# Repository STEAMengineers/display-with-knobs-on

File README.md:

# display-with-knobs-on

Think [cheap yellow display](https://github.com/witnessmenow/ESP32-Cheap-Yellow-Display) but not necessarily yellow and with two joystick inputs and four channels of brushed motor output. Originally designed to control [The open source underwater vehicle](https://github.com/concretedog/Tiny-Opensource-Underwater-Vehicle-TOUV-) project. 

## Features

* [RP2350b](https://datasheets.raspberrypi.com/rp2350/rp2350-product-brief.pdf) - Dual Arm Cortex-M33 or dual Hazard3 RISC-V processors
@ 150MHz
* [W25Q128JV-DTR](https://www.winbond.com/resource-files/w25q128jv_dtr%20revc%2003272018%20plus.pdf) - 16Mb primary flash 
* [MSP3520 screen](https://www.lcdwiki.com/3.5inch_SPI_Module_ILI9488_SKU%3AMSP3520) - ILI9488 powered 320x480 LCD screen with resistive touch and SD card slot (Headers)
* 2 x [TB6612FNG](https://toshiba.semicon-storage.com/us/product/linear/motordriver/detail.TB6612FNG.html) - Four channels of brushed motor outputs
* [IP5310](https://www.injoinic.com/api//static/uploads/20250528/20250528180445_6836dfbd54166.pdf) - Battery charger management with 3A boost output @ 5V for motors
* 2 x Joystick - Two axis analoge joysticks with push button inputs

  ## GPIO

  ### Motors

  A
  * IN1 - GPIO29
  * IN2 - GPIO28
  * PWM - GPIO24

  B
  * IN1 - GPIO31
  * IN2 - GPIO32
  * PWM - GPIO25

  STANDBY - GPIO30

  C
  * IN1 - GPIO34
  * IN2 - GPIO33
  * PWM - GPIO26

  D
  * IN1 - GPIO36
  * IN2 - GPIO37
  * PWM - GPIO27

  STANDBY - GPIO35

  ### Joysticks
  A
  * X - GPIO43
  * Y - GPIO44
  * Button - GPIO39
 
  B
  * X - GPIO41
  * Y - GPIO42
  * Button - GPIO38
 
  ### Screen

  Display
  * CS - GPIO13
  * RESET - GPIO18
  * DC/RS - GPIO17
  * MOSI - GPIO11
  * MISO - GPIO12
  * SCK - GPIO14
  * LED - GPIO16
 
  Touch
  * CS - GPIO10
  * IRQ - GPIO15
  * MOSI - GPIO11
  * MISO - GPIO12
  * SCK - GPIO14
 
  SD card
  * CS - GPIO21
  * SCK - GPIO22
  * MOSI - GPIO19
  * MISO - GPIO20

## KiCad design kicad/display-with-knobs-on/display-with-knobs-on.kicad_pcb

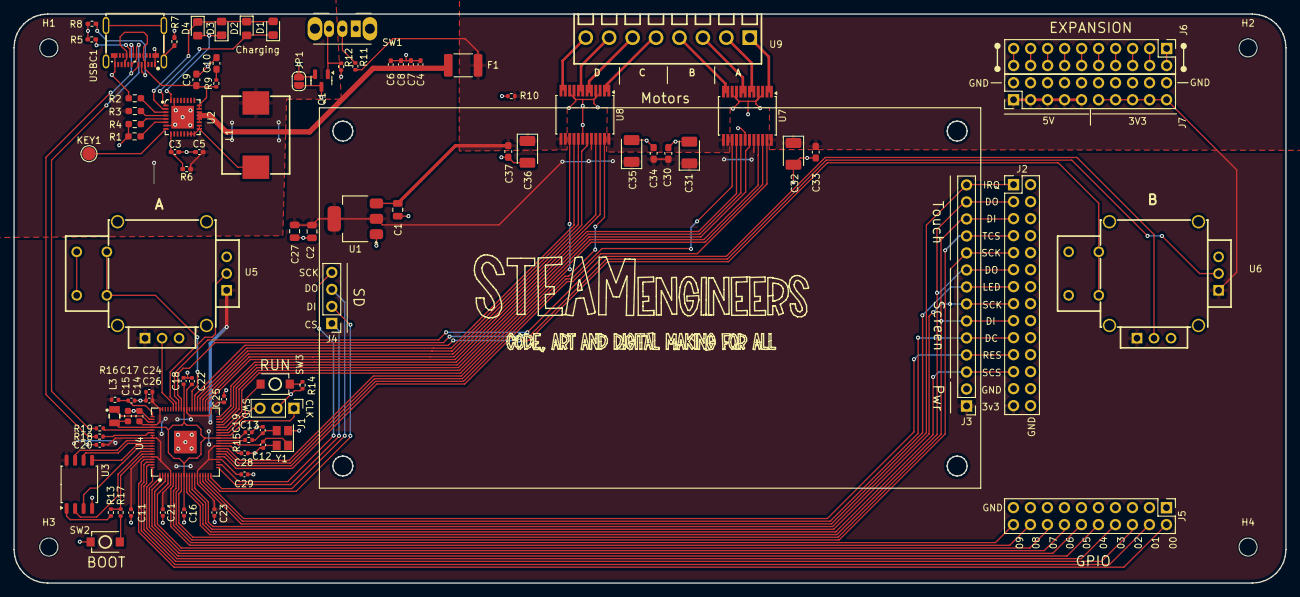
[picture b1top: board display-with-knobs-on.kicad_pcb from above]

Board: 2 copper layers, 190.0 x 85.0 mm, 92 parts (1 on the bottom side), 106 nets.

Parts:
C1, C2, C27: 10u; C_0805_2012Metric
C3, C4, C5, C6, C7, C8: 22uF; C_0402_1005Metric_Pad0.74x0.62mm_HandSolder
C9, C10: 10uF; C_0603_1608Metric_Pad1.08x0.95mm_HandSolder
C11, C16, C19, C20, C21, C22, C23, C24, C25, C26, C28, C29: 100n; C_0402_1005Metric
C12, C13: 15p; C_0402_1005Metric
C14, C15: 4.7u; C_0603_1608Metric
C17, C18: 4.7u; C_0402_1005Metric
C30, C33, C34, C37: 0.1uF; C_0603_1608Metric_Pad1.08x0.95mm_HandSolder
C31, C32, C35, C36: 10uF; CP_EIA-3528-21_Kemet-B_Pad1.50x2.35mm_HandSolder
CN1: S2B-PH-SM4-TB(LF)(SN); CONN-SMD_P2.00_S2B-PH-SM4-TB-LF-SN
D1, D2, D3, D4: LED; LED_0805_2012Metric_Pad1.15x1.40mm_HandSolder
F1: Polyfuse; Fuse_1812_4532Metric_Pad1.30x3.40mm_HandSolder
H1, H2, H3, H4: MountingHole; MountingHole_2.7mm_M2.5
J1: Conn_01x03_Pin; PinHeader_1x03_P2.54mm_Vertical
J2: Conn_02x14_Odd_Even; PinHeader_2x14_P2.54mm_Vertical
J3: Conn_01x14_Socket; PinHeader_1x14_P2.54mm_Vertical
J4: Conn_01x04_Socket; PinHeader_1x04_P2.54mm_Vertical
J5, J6, J7: Conn_02x10_Odd_Even; PinHeader_2x10_P2.54mm_Vertical
JP1: Jumper_on; SolderJumper-2_P1.3mm_Open_RoundedPad1.0x1.5mm
KEY1: TestPoint; TestPoint_Pad_D2.0mm
L1: MHCC10040-1R0M-R7; IND-SMD_L11.6-W10.1
L3: 3.3u; IND-SMD_L2.0-W1.6_AOTA-B201610S3R3-101-T
Q1: JSM2302; SOT-23
R1: 51K; R_0603_1608Metric_Pad0.98x0.95mm_HandSolder
R2, R3, R4: 0; R_0603_1608Metric_Pad0.98x0.95mm_HandSolder
R5, R8: 5.1K; R_0402_1005Metric_Pad0.72x0.64mm_HandSolder
R6: 0; R_0402_1005Metric_Pad0.72x0.64mm_HandSolder
R7: 1M; R_0402_1005Metric_Pad0.72x0.64mm_HandSolder
R9: 2R; R_0402_1005Metric
R10: R120; R_0402_1005Metric
R11: 10K; R_0402_1005Metric
R12: 100K; R_0402_1005Metric
R13: 0; R_0402_1005Metric
R14, R15, R17: 1k; R_0402_1005Metric
R16: 33; R_0402_1005Metric
R18, R19: 27; R_0402_1005Metric
SW1: ON/OFF; SW_Slide_SPDT_Angled_CK_OS102011MA1Q
SW2, SW3: SW_Push; SW-SMD_L3.9-W3.0-P4.45
U1: NCP1117-3.3_SOT223; SOT-223-3_TabPin2
U2: IP5310; QFN-32_L5.0-W5.0-P0.50-BL-EP3.4
U3: W25Q128JVS; SOIC-8_5.23x5.23mm_P1.27mm
U4: RP2350_80QFN; QFN-80_L10.0-W10.0-P0.40-TL-EP3.4
U5, U6: YF16S-FL7.2-B5KB(45-10)-Y; JOYTICK-TH_YF16S-FL7.2-B5KB-45-10-Y_1
U7, U8: TB6612FNG; SSOP-24_5.3x8.2mm_P0.65mm
U9: DB125-3.5-8P-GN-S; CONN-TH_8P-P3.50_DORABO_DB125-3.5-8P-GN-S
USBC1: 105450-0101; USB-C-SMD_TYPE-C-USB-18
Y1: ABM8-272-T3; Crystal_SMD_3225-4Pin_3.2x2.5mm

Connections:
+1V1: C15.1, C16.1, C18.1, C19.1, L3.1, U4.10 (DVDD), U4.32 (DVDD), U4.51 (DVDD), U4.65 (VREG_FB)
+3V3: C2.1, C11.1, C14.1, C20.1, C21.1, C22.1, C23.1, C24.1, C25.1, C26.1, C27.1, C28.1, C29.1, C30.1, C31.1, C34.1, C35.1, J2.27, J3.1, J7.11, J7.13, J7.15, J7.17, J7.19, R16.1, U1.2 (VO), U3.8 (VCC), U4.5 (IOVDD), U4.15 (IOVDD), U4.24 (IOVDD), U4.29 (IOVDD), U4.41 (IOVDD), U4.50 (IOVDD), U4.59 (ADC_AVDD), U4.60 (IOVDD), U4.64 (VREG_VIN), U4.68 (USB_OTP_VDD), U4.69 (QSPI_IOVDD), U4.76 (IOVDD), U5.1, U5.4, U6.1, U6.4, U7.20 (VCC), U8.20 (VCC)
+5V: C1.1, C32.1, C33.1, C36.1, C37.1, F1.1, J7.1, J7.3, J7.5, J7.7, J7.9, R10.2, R11.1, U1.3 (VI), U7.13 (VM2), U7.14 (VM3), U7.24 (VM1), U8.13 (VM2), U8.14 (VM3), U8.24 (VM1)
+BATT: C5.1, CN1.2, L1.2, R3.1, R6.1
-BATT: C3.2, C4.2, C5.2, C6.2, C7.2, C8.2, C9.2, C10.2, CN1.1, JP1.1, Q1.2 (S), R1.1, R2.1, R4.1, R5.2, R7.2, R8.2, R12.2, U2.7 (AGND), U2.31 (LIGHT), U2.33 (EP), USBC1.A1 (GND), USBC1.A12 (GND), USBC1.B1 (GND), USBC1.B12 (GND)
/Controller/FLASH_SS: R13.2, U3.1 (~CS)
/Controller/QSPI_SCLK: U3.6 (CLK), U4.71 (QSPI_SCLK)
/Controller/QSPI_SD0: U3.5 (DI(IO0)), U4.72 (QSPI_SD0)
/Controller/QSPI_SD1: U3.2 (DO(IO1)), U4.74 (QSPI_SD1)
/Controller/QSPI_SD2: U3.3 (IO2), U4.73 (QSPI_SD2)
/Controller/QSPI_SD3: U3.7 (IO3), U4.70 (QSPI_SD3)
/Controller/QSPI_SS: R13.1, R17.1, U4.75 (QSPI_SS)
/Controller/RUN: SW3.2, U4.35 (RUN)
/Controller/VREG_AVDD: C17.1, R16.2, U4.61 (VREG_AVDD)
/Controller/VREG_LX: L3.2, U4.63 (VREG_LX)
/Controller/XIN: C12.1, U4.30 (XIN), Y1.1
/Controller/XOUT: R15.1, U4.31 (XOUT)
/Controller/~USB_BOOT: R17.2, SW2.2
/Power/VBUS: C9.1, R9.1, U2.23 (VIN), U2.24 (VIN), USBC1.A4 (VBUS), USBC1.A9 (VBUS), USBC1.B4 (VBUS), USBC1.B9 (VBUS)
A1: U7.1 (AO1), U7.2 (AO1), U9.1
A2: U7.5 (AO2), U7.6 (AO2), U9.2
ABUTTON: U4.48 (GPIO39), U5.8
AIN1: U4.37 (GPIO29), U7.21 (AIN1)
AIN2: U4.36 (GPIO28), U7.22 (AIN2)
AX: U4.54 (GPIO43_ADC3), U5.5
AY: U4.55 (GPIO44_ADC4), U5.2
B1: U7.11 (BO1), U7.12 (BO1), U9.4
B2: U7.7 (BO2), U7.8 (BO2), U9.3
BBUTTON: U4.47 (GPIO38), U6.8
BIN1: U4.39 (GPIO31), U7.17 (BIN1)
BIN2: U4.40 (GPIO32), U7.16 (BIN2)
BX: U4.52 (GPIO41_ADC1), U6.5
BY: U4.53 (GPIO42_ADC2), U6.2
C1: U8.1 (AO1), U8.2 (AO1), U9.5
C2: U8.5 (AO2), U8.6 (AO2), U9.6
CC1: R8.1, USBC1.A5 (CC1)
CC2: R5.1, USBC1.B5 (CC2)
CIN1: U4.43 (GPIO34), U8.21 (AIN1)
CIN2: U4.42 (GPIO33), U8.22 (AIN2)
D1: U8.11 (BO1), U8.12 (BO1), U9.8
D2: U8.7 (BO2), U8.8 (BO2), U9.7
D+: R18.1, USBC1.A6 (D+), USBC1.B6 (D+)
D-: R19.1, USBC1.A7 (D-), USBC1.B7 (D-)
DIN1: U4.45 (GPIO36), U8.17 (BIN1)
DIN2: U4.46 (GPIO37), U8.16 (BIN2)
GND: C1.2, C2.2, C11.2, C12.2, C13.2, C14.2, C15.2, C16.2, C17.2, C18.2, C19.2, C20.2, C21.2, C22.2, C23.2, C24.2, C25.2, C26.2, C27.2, C28.2, C29.2, C30.2, C31.2, C32.2, C33.2, C34.2, C35.2, C36.2, C37.2, J1.2, J2.2, J2.4, J2.6, J2.8, J2.10, J2.12, J2.14, J2.16, J2.18, J2.20, J2.22, J2.24, J2.25, J2.26, J2.28, J3.2, J5.1, J5.3, J5.5, J5.7, J5.9, J5.11, J5.13, J5.15, J5.17, J5.19, J7.2, J7.4, J7.6, J7.8, J7.10, J7.12, J7.14, J7.16, J7.18, J7.20, JP1.2, Q1.3 (D), R10.1, R14.2, SW2.1, U1.1 (GND), U3.4 (GND), U4.62 (VREG_PGND), U4.81 (GND), U5.3, U5.6, U5.7, U6.3, U6.6, U6.7, U7.3 (PGND1), U7.4 (PGND1), U7.9 (PGND2), U7.10 (PGND2), U7.18 (GND), U8.3 (PGND1), U8.4 (PGND1), U8.9 (PGND2), U8.10 (PGND2), U8.18 (GND), Y1.2, Y1.4
GPIO_0: J5.2, U4.77 (GPIO0)
GPIO_1: J5.4, U4.78 (GPIO1)
GPIO_2: J5.6, U4.79 (GPIO2)
GPIO_3: J5.8, U4.80 (GPIO3)
GPIO_4: J5.10, U4.1 (GPIO4)
GPIO_5: J5.12, U4.2 (GPIO5)
GPIO_6: J5.14, U4.3 (GPIO6)
GPIO_7: J5.16, U4.4 (GPIO7)
GPIO_8: J5.18, U4.6 (GPIO8)
GPIO_9: J5.20, U4.7 (GPIO9)
unnamed: C4.1, C6.1, C7.1, C8.1, F1.2, U2.19 (VOUT), U2.20 (VOUT), U2.21 (VOUT), U2.22 (VOUT)
unnamed: C10.1, R9.2
unnamed: C13.1, R15.2, Y1.3
unnamed: D1.2 (A), D2.1 (K), D3.2 (A), D4.1 (K), U2.2 (L3)
unnamed: D1.1 (K), D2.2 (A), U2.1 (L2)
unnamed: D3.1 (K), D4.2 (A), U2.32 (L1)
unnamed: J6.1, J6.2
unnamed: J6.3, J6.4
unnamed: J6.5, J6.6
unnamed: J6.7, J6.8
unnamed: J6.9, J6.10
unnamed: J6.11, J6.12
unnamed: J6.13, J6.14
unnamed: J6.15, J6.16
unnamed: J6.17, J6.18
unnamed: J6.19, J6.20
unnamed: L1.1, U2.14 (LX), U2.15 (LX), U2.16 (LX), U2.17 (LX), U2.18 (LX)
unnamed: Q1.1 (G), R12.1, SW1.3 (C)
unnamed: R14.1, SW3.1
unnamed: R11.2, SW1.2 (B)
unnamed: C3.1, R6.2, U2.9 (BAT)
unnamed: KEY1.1, U2.8 (KEY)
unnamed: R1.2, U2.6 (NTC)
unnamed: R4.2, U2.5 (RSET)
unnamed: R2.2, U2.3 (VSET)
unnamed: R3.2, U2.4 (VTHS)
unnamed: R19.2, U4.66 (USB_DM)
unnamed: R18.2, U4.67 (USB_DP)
unnamed: R7.1, USBC1.0
PWMA: U4.25 (GPIO24), U7.23 (PWMA)
PWMB: U4.26 (GPIO25), U7.15 (PWMB)
PWMC: U4.27 (GPIO26), U8.23 (PWMA)
PWMD: U4.28 (GPIO27), U8.15 (PWMB)
SC_CS: J2.23, J3.3, U4.12 (GPIO13)
SC_DC_RS: J2.19, J3.5, U4.17 (GPIO17)
SC_LED: J2.13, J3.8, U4.16 (GPIO16)
SC_RESET: J2.21, J3.4, U4.18 (GPIO18)
SC_SCK: J2.9, J2.15, J3.7, J3.10, U4.13 (GPIO14)
SC_SDI_MOSI: J2.5, J2.17, J3.6, J3.12, U4.9 (GPIO11)
SC_SDO_MISO: J2.3, J2.11, J3.9, J3.13, U4.11 (GPIO12)
SC_TS_CS: J2.7, J3.11, U4.8 (GPIO10)
SC_TS_IRQ: J2.1, J3.14, U4.14 (GPIO15)
SD_CS: J4.1, U4.21 (GPIO21)
SD_MISO: J4.3, U4.20 (GPIO20)
SD_MOSI: J4.2, U4.19 (GPIO19)
SD_SCK: J4.4, U4.22 (GPIO22)
STBY_A: U4.38 (GPIO30), U7.19 (STBY)
STBY_B: U4.44 (GPIO35), U8.19 (STBY)
SWCLK: J1.1, U4.33 (SWCLK)
SWD: J1.3, U4.34 (SWD)

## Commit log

2025-07-31 Add features desc to readme
2025-07-31 Add joystick key design for TPU
2025-07-31 Documentation
2025-07-31 Initial hardware commit
2025-07-31 Initial firmware commit
2025-07-31 Added licence
2025-08-01 First screen lib tests
2025-08-01 Tidy old code
2025-08-03 First LVGL code
2025-08-03 Animation files
2025-08-03 uf2 snapshot for sharing purposes
2025-08-05 Refactor motor functions, fix differential drive
2025-08-05 Add Snoofs graphics
2025-08-05 New slider graphics implemented in x an y
2025-08-05 Update sharing uf2 file to latest version
2025-08-07 Reorder layout, include new grpahics
2025-08-07 Update uf2 to current build
2025-10-10 Add new background image
